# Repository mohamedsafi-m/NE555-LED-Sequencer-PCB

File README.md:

# NE555 LED Sequencer PCB

A PCB-based LED sequencing circuit built using two NE555 timer ICs.  
The circuit generates oscillating signals to drive multiple LEDs in a pattern.

## Overview

This project implements an LED sequencing circuit using two NE555 timers.
One timer generates the clock signal, while the second timer controls the LED switching pattern.

The design was created as part of a hands-on learning exercise in:

- Analog electronics
- Timer circuits
- PCB design
- KiCad schematic and layout
## Features

- Dual NE555 timer based circuit
- LED sequencing effect
- Custom designed PCB
- Simple analog timing control
- Easy to assemble with through-hole components

## Circuit Description

The circuit consists of two NE555 timer ICs:

Timer 1 (Astable Mode)
- Generates a clock signal
- Frequency controlled using resistor R1 and capacitor C1

Timer 2
- Uses the clock signal to drive LED outputs

LED arrays are arranged on both sides of the PCB to create a visual sequencing pattern.
## How to Use

1. Open the project in KiCad
2. Review the schematic and PCB layout
3. Generate Gerber files
4. Send them to a PCB manufacturer
5. Assemble the components

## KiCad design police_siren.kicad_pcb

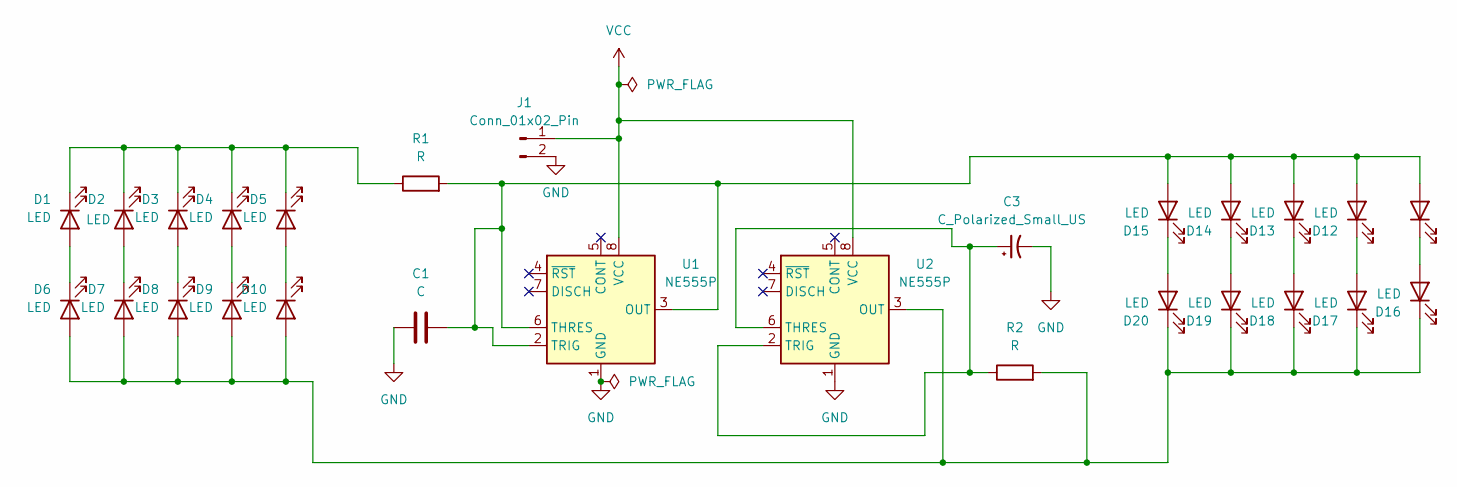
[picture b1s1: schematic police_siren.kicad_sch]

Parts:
C1: C; CP_Radial_D4.0mm_P1.50mm
C3: C_Polarized_Small_US; CP_Radial_D4.0mm_P1.50mm
D1, D2, D3, D4, D5, D6, D7, D8, D9, D10, D11, D12, D13, D14, D15, D16, D17, D18, D19, D20: LED; LED_D3.0mm
J1: Conn_01x02_Pin; PinSocket_1x02_P2.54mm_Vertical
R1, R2: R; R_Axial_DIN0204_L3.6mm_D1.6mm_P5.08mm_Horizontal
U1, U2: NE555P; DIP-8_W7.62mm

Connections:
GND: C1.2, C3.2, J1.2, U1.1 (GND), U2.1 (GND)
unnamed: D1.2 (A), D6.1 (K)
unnamed: D1.1 (K), D2.1 (K), D3.1 (K), D4.1 (K), D5.1 (K), R1.1
unnamed: D2.2 (A), D7.1 (K)
unnamed: D3.2 (A), D8.1 (K)
unnamed: D4.2 (A), D9.1 (K)
unnamed: D6.2 (A), D7.2 (A), D8.2 (A), D9.2 (A), D10.2 (A), D16.1 (K), D17.1 (K), D18.1 (K), D19.1 (K), D20.1 (K), R2.2, U2.3 (OUT)
unnamed: D5.2 (A), D10.1 (K)
unnamed: C1.1, D11.2 (A), D12.2 (A), D13.2 (A), D14.2 (A), D15.2 (A), R1.2, U1.2 (TRIG), U1.3 (OUT), U1.6 (THRES)
unnamed: D11.1 (K), D16.2 (A)
unnamed: D12.1 (K), D17.2 (A)
unnamed: D13.1 (K), D18.2 (A)
unnamed: D14.1 (K), D19.2 (A)
unnamed: D15.1 (K), D20.2 (A)
unnamed: C3.1, R2.1, U2.2 (TRIG), U2.6 (THRES)
VCC: J1.1, U1.8 (VCC), U2.8 (VCC)

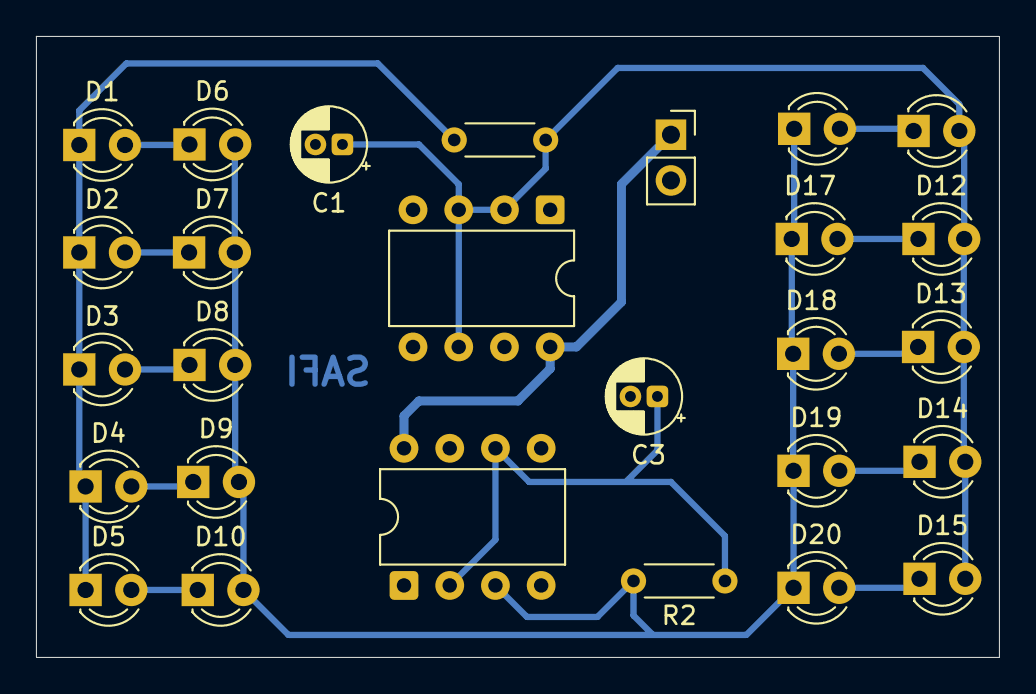
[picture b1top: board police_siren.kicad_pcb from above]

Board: 2 copper layers, 53.5 x 34.5 mm, 27 parts (0 on the bottom side), 16 nets.

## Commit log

2026-03-13 Update README with NE555 LED Sequencer details
    Added project overview, features, circuit description, and usage instructions for NE555 LED Sequencer PCB.
2026-03-13 Fix formatting of assembly step in README
